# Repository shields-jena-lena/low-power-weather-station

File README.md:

# low-power-weather-station
Circuity and code for a low-power weather station design used for agricultural research

Build instructions will be available in Hardware X article once published

https://doi.org/10.5281/zenodo.22212162

# File summaries:

## 3.1	Arduino_code: different code versions to upload to weather station boards
  -	weatherstation_v2.ino
    - Arduino code to run the second version of the weather station build, this version allows for sleep.
  -	weatherstation_v2_constant.ino
    - Arduino code to run the second version of the weather station build, data is taken continuously.
  -	weatherstation_v5.ino
    -	Arduino code the run the 5th version of the weather station build, this version allows sleep and includes more code for low power optimization.
  -	Weatherstation_v5_constant.ino
    -	Arduino code to run the 5th version of the weather station build, data is taken continuously.

## 3.2	CAD_files: .stl files for 3D printed sensor box
  -	Humidity box bottom 1.stl
    -	STL file to print the bottom half of the box to hold the humidity and temperature sensor.
  -	Humidity box top 1.stl
    - STL file to print the top half of the box to hold the humidity and temperature sensor.

## 3.3	KiCAD_files: Circuit design and PCB design for custom circuity for weather stations
  -	Libraries
    -	Footprints and symbols for electronic components custom designed or downloaded from digikey.
  -	weather_station_v2
    -	Complete KiCAD project files for the design and PCB layout of the 2nd version of the weather station. Includes the schematic, project file, board design, bill of materials, backups, custom_footprints, and gerber files.
  -	weather_station_v5
    -	Complete KiCAD project files for the design and PCB layout of the 5th version of the weather station. Includes the schematic, project file, board design, bill of materials, backups, and gerber files.
      
## 3.4	Matlab_code – Matlab scripts to calibrate, process, and analyze weather station data, includes sample data
  -	txtfile_to_table.m
    -	MATLAB script to convert raw data from Arduino output to a .mat table.
  -	txtfile_to_table_parpool.m
    -	MATLAB script to convert raw data from Arduino output to a .mat table, using parpool to loop through all raw data in one script.
  -	std_omidNaN.m
    -	Custom function to support other MATLAB scripts that need the standard deviation while omitting NaN values.
  -	makebigarray.m
    -	MATLAB script to take the .mat tables of each weather station and combine into a large array with data from all the stations.
  -	field_analysis.m
    -	MATLAB script to do some basic analysis on the data in the large array created by makebigarray.m.
  -	calibrate_cupanemometer.m 
    - MATLAB script to calibrate cup anemometers if you have test chamber with known wind speed and raw cup count data from the weather stations. 
  -	sample_data (Both in Matlab_code/ and in Python_code/)
    - Raw text file data from weather stations. Each data file is labeled “weather_station_b#” where # is the number of the station. Data from stations 3 through 7 is included. The station_heights.csv file reports the height of the wind measurements and temperature/humidity measurements for each station. The image field28_layout_8-29-23 shows the relative location of each station to each other. The calibration_data folder includes raw data from each weather station in a testing chamber with known wind speed.
       
## 3.5	Python_code – Python scripts to calibrate, process, and analyze wather station data, includes sample data
  -	txtfile_to_table.py
    -	Python script to convert raw data from weather station to .csv file. 
  -	txtfile_to_table_forloop.py
    -	Python script to convert raw data from weather station to .csv file, a for loop is used to loop through all weather stations in one script.
  -	makebigarray.py
    -	Python script to take the .csv tables of each weather station and combine into a large array with data from all the stations.
  -	fieldanalysis.py
    -	Python script to take the output of makebigarray.py and do some basic analysis.
  -	calibrate_cupanemometer.py
    -	Python script to calibrate cup anemometer if you have test chamber with known wind speed and raw cup count data from the weather stations. 
  -	sample_data (Both in Matlab_code/ and in Python_code/)
    -	Raw text file data from weather stations. Each data file is labeled “weather_station_b#” where # is the number of the station. Data from stations 3 through 7 is included. The station_heights.csv file reports the height of the wind measurements and temperature/humidity measurements for each station. The image field28_layout_8-29-23 shows the relative location of each station to each other. The calibration_data folder includes raw data from each weather station in a testing chamber with known wind speed.

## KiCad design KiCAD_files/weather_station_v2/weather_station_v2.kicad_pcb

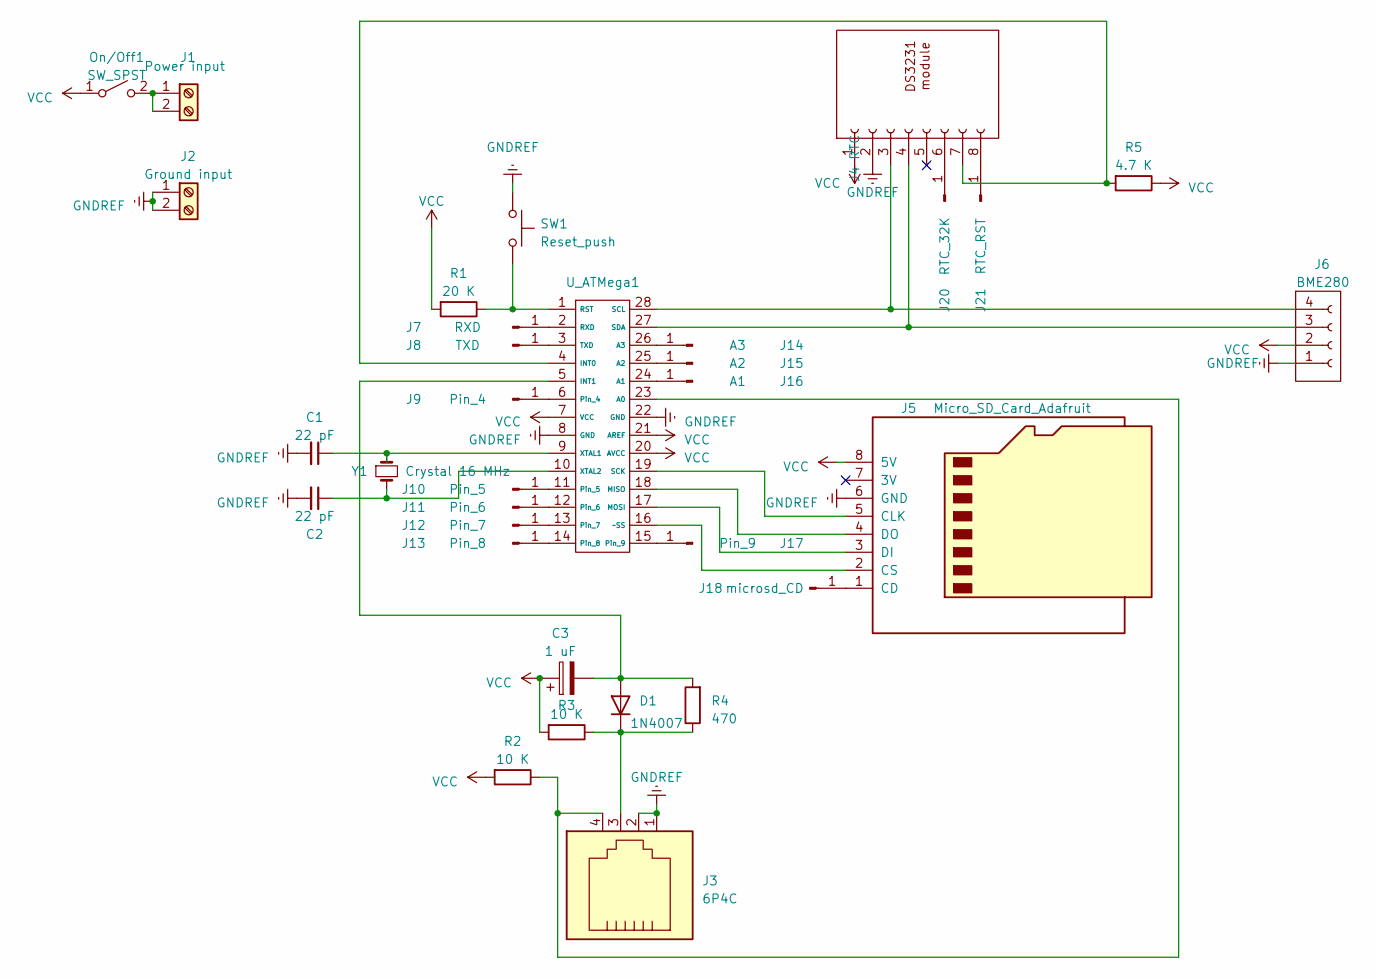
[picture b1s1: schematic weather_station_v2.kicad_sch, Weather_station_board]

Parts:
C1, C2: 22 pF; C_1206_3216Metric_Pad1.33x1.80mm_HandSolder
C3: 1 uF; C_Elec_4x5.4
D1: 1N4007; D_SOD-123F
J1: Power input; Term_Block_1x2_P5.08MM
J2: Ground input; Term_Block_1x2_P5.08MM
J3: 6P4C; RJ11_connector_jack
J4: RTC; PinSocket_1x08_P2.54mm_Vertical_RTC
J5: Micro_SD_Card_Adafruit; adafruit_microSD_breakout_board_8-pin
J6: BME280; JST-SH
J7: RXD; Pin_D1.0mm_L10.0mm
J8: TXD; Pin_D1.0mm_L10.0mm
J9: Pin_4; Pin_D1.0mm_L10.0mm
J10: Pin_5; Pin_D1.0mm_L10.0mm
J11: Pin_6; Pin_D1.0mm_L10.0mm
J12: Pin_7; Pin_D1.0mm_L10.0mm
J13: Pin_8; Pin_D1.0mm_L10.0mm
J14: A3; Pin_D1.0mm_L10.0mm
J15: A2; Pin_D1.0mm_L10.0mm
J16: A1; Pin_D1.0mm_L10.0mm
J17: Pin_9; Pin_D1.0mm_L10.0mm
J18: microsd_CD; Pin_D1.0mm_L10.0mm
J20: RTC_32K; Pin_D1.0mm_L10.0mm
J21: RTC_RST; Pin_D1.0mm_L10.0mm
On/Off1: SW_SPST; Switch_Slide_SPST_DS04-254-2-01BK-SMT
R1: 20 K; R_1206_3216Metric_Pad1.30x1.75mm_HandSolder
R2, R3: 10 K; R_1206_3216Metric_Pad1.30x1.75mm_HandSolder
R4: 470; R_1206_3216Metric_Pad1.30x1.75mm_HandSolder
R5: 4.7 K; R_1206_3216Metric_Pad1.30x1.75mm_HandSolder
SW1: Reset_push; SW_Tactile_SPST_NO_Straight_CK_PTS636Sx25SMTRLFS
U_ATMega1: Socket_DIP-28_7.62mm_Conn
Y1: Crystal 16 MHz; Crystal_HC18-U_Vertical

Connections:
GNDREF: C1.2, C2.2, J2.1, J2.2, J3.1, J3.2, J4.2 (GND), J5.6 (GND), J6.1, SW1.1, U_ATMega1.8 (GND), U_ATMega1.22 (GND)
unnamed: C3.2, D1.2 (A), R4.2, U_ATMega1.5 (INT1)
unnamed: D1.1 (K), J3.3, R3.1, R4.1
unnamed: J1.1, J1.2, On/Off1.2 (B)
unnamed: J4.3 (SCL), J6.4, U_ATMega1.28 (SCL)
unnamed: J4.4 (SDA), J6.3, U_ATMega1.27 (SDA)
unnamed: J4.7 (SQW), R5.2, U_ATMega1.4 (INT0)
unnamed: J5.5 (CLK), U_ATMega1.19 (SCK)
unnamed: J5.2 (CS), U_ATMega1.16 (~SS)
unnamed: J5.3 (DI), U_ATMega1.17 (MOSI)
unnamed: J5.4 (DO), U_ATMega1.18 (MISO)
unnamed: J7.1, U_ATMega1.2 (RXD)
unnamed: J8.1, U_ATMega1.3 (TXD)
unnamed: J9.1, U_ATMega1.6 (Pin_4)
unnamed: J10.1, U_ATMega1.11 (Pin_5)
unnamed: J11.1, U_ATMega1.12 (Pin_6)
unnamed: J12.1, U_ATMega1.13 (Pin_7)
unnamed: J13.1, U_ATMega1.14 (Pin_8)
unnamed: J14.1, U_ATMega1.26 (A3)
unnamed: J15.1, U_ATMega1.25 (A2)
unnamed: J16.1, U_ATMega1.24 (A1)
unnamed: J17.1, U_ATMega1.15 (Pin_9)
unnamed: J5.1 (CD), J18.1
unnamed: J4.6 (32K), J20.1
unnamed: J4.8 (RST), J21.1
unnamed: J3.4, R2.1, U_ATMega1.23 (A0)
unnamed: R1.1, SW1.2, U_ATMega1.1 (RST)
unnamed: C1.1, U_ATMega1.9 (XTAL1), Y1.1
unnamed: C2.1, U_ATMega1.10 (XTAL2), Y1.2
VCC: C3.1, J4.1 (Vin), J5.8 (5V), J6.2, On/Off1.1 (A), R1.2, R2.2, R3.2, R5.1, U_ATMega1.7 (VCC), U_ATMega1.20 (AVCC), U_ATMega1.21 (AREF)

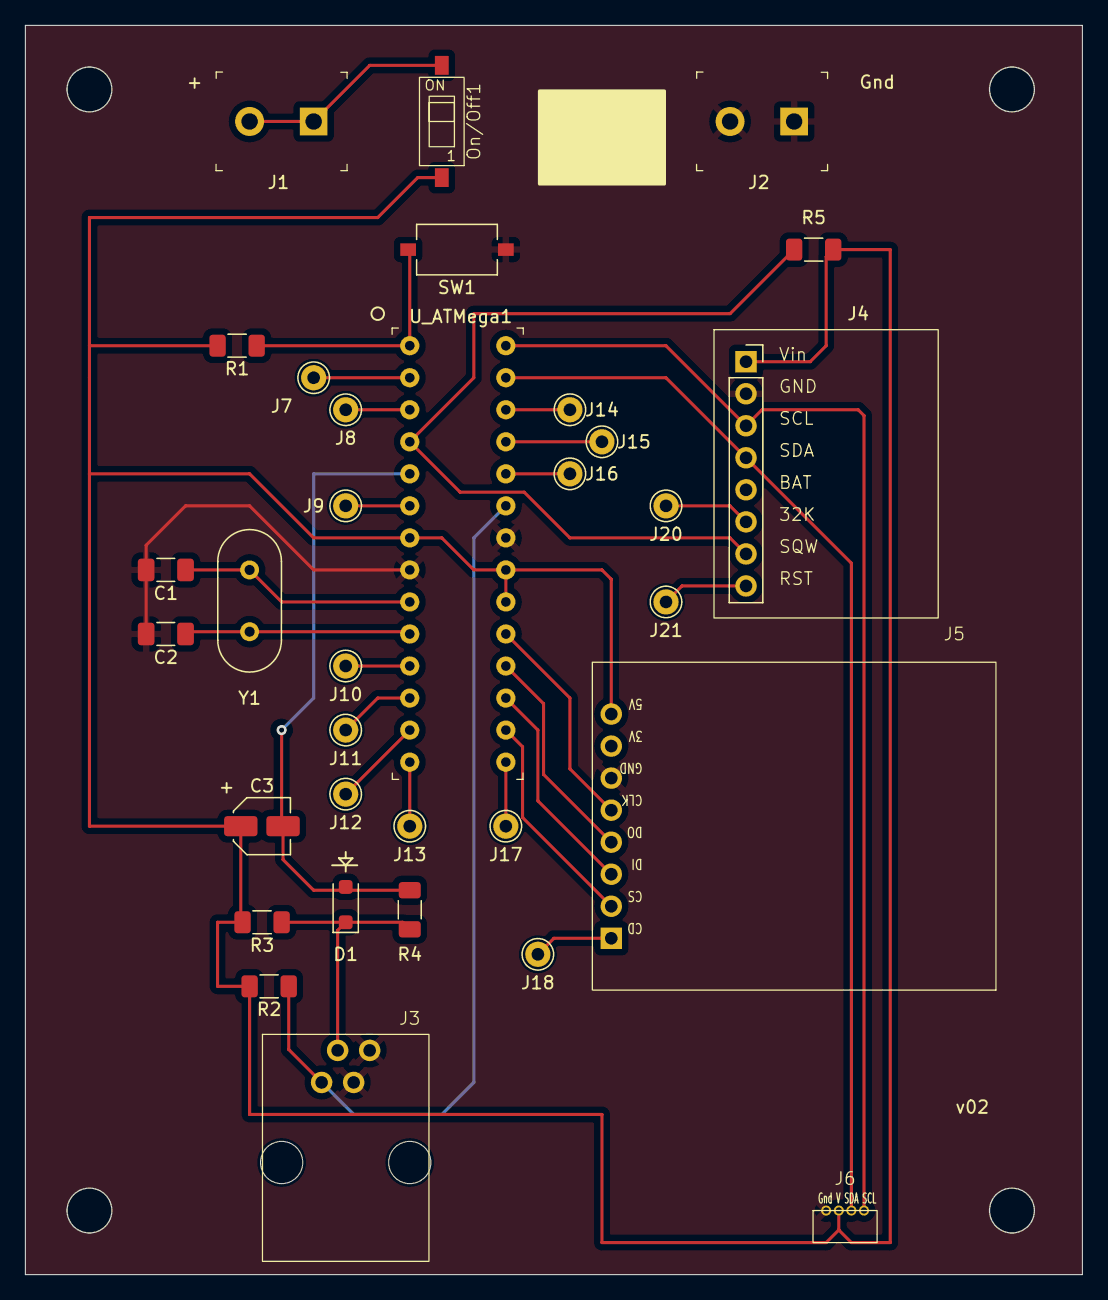
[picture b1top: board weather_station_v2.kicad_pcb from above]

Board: 2 copper layers, 83.7 x 99.0 mm, 33 parts (0 on the bottom side), 30 nets.

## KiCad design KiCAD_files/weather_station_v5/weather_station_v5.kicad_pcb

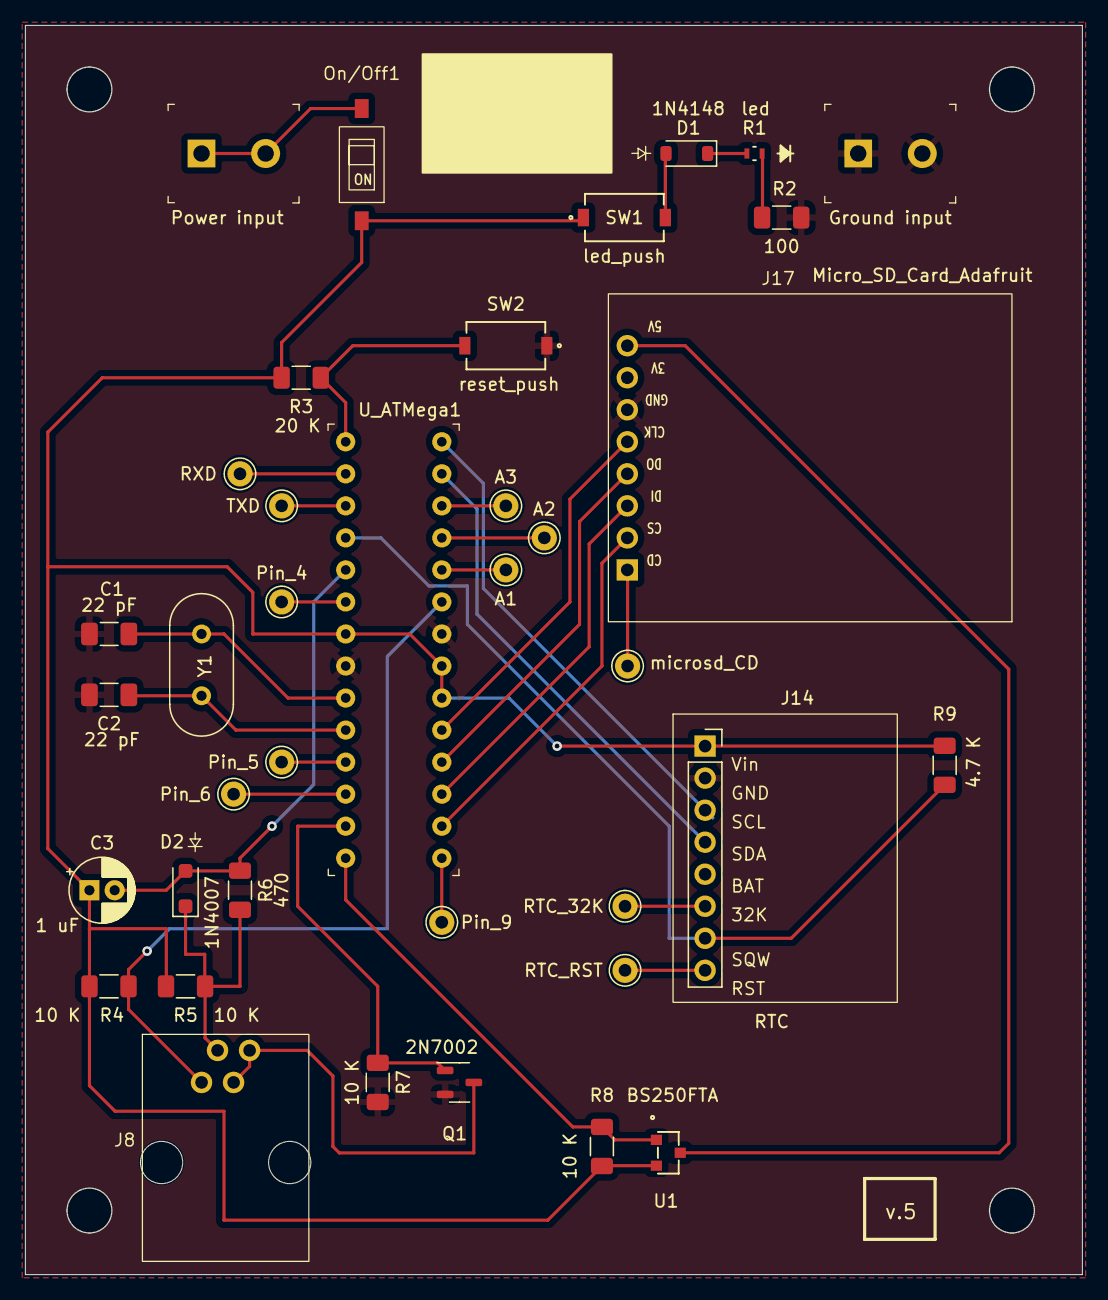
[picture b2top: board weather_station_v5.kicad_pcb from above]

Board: 2 copper layers, 83.7 x 99.0 mm, 38 parts (0 on the bottom side), 35 nets.

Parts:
C1, C2: 22 pF; C_1206_3216Metric_Pad1.33x1.80mm_HandSolder
C3: 1 uF; CP_Radial_D5.0mm_P2.00mm
D1: 1N4148; D_SOD-123
D2: 1N4007; D_SOD-123F
J1: Power input; Term_Block_1x2_P5.08MM
J2: Ground input; Term_Block_1x2_P5.08MM
J3: RXD; Pin_D1.0mm_L10.0mm
J4: TXD; Pin_D1.0mm_L10.0mm
J5: Pin_4; Pin_D1.0mm_L10.0mm
J6: Pin_5; Pin_D1.0mm_L10.0mm
J7: Pin_6; Pin_D1.0mm_L10.0mm
J8: 6P4C; RJ11_connector_jack
J9: A3; Pin_D1.0mm_L10.0mm
J10: A2; Pin_D1.0mm_L10.0mm
J11: A1; Pin_D1.0mm_L10.0mm
J12: Pin_9; Pin_D1.0mm_L10.0mm
J13: microsd_CD; Pin_D1.0mm_L10.0mm
J14: RTC; PinSocket_1x08_P2.54mm_Vertical_RTC
J15: RTC_32K; Pin_D1.0mm_L10.0mm
J16: RTC_RST; Pin_D1.0mm_L10.0mm
J17: Micro_SD_Card_Adafruit; adafruit_microSD_breakout_board_8-pin
On/Off1: SW_SPST; Switch_Slide_SPST_DS04-254-2-01BK-SMT
Q1: 2N7002; SOT-23-3
R1: led; LED_SMLD12_ROM
R2: 100; R_1206_3216Metric_Pad1.30x1.75mm_HandSolder
R3: 20 K; R_1206_3216Metric_Pad1.30x1.75mm_HandSolder
R4, R5, R7, R8: 10 K; R_1206_3216Metric_Pad1.30x1.75mm_HandSolder
R6: 470; R_1206_3216Metric_Pad1.30x1.75mm_HandSolder
R9: 4.7 K; R_1206_3216Metric_Pad1.30x1.75mm_HandSolder
SW1: led_push; SW_PTS636_CNK
SW2: reset_push; SW_PTS636_CNK
U1: BS250FTA; SOT-23_DIO
U_ATMega1: Socket_DIP-28_7.62mm_Conn
Y1: Crystal 16 MHz; Crystal_HC18-U_Vertical

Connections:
GNDREF: C1.2, C2.2, J2.1, J2.2, J14.2 (GND), J17.6 (GND), Q1.2 (S), R2.2, R7.2, SW2.1, U_ATMega1.8 (GND), U_ATMega1.22 (GND)
unnamed: D1.2 (A), SW1.2
unnamed: D1.1 (K), R1.2
unnamed: C3.2, D2.2 (A), R6.2, U_ATMega1.5 (INT1)
unnamed: D2.1 (K), J8.3, R5.1, R6.1
unnamed: J1.1, J1.2, On/Off1.2 (B)
unnamed: J3.1, U_ATMega1.2 (RXD)
unnamed: J4.1, U_ATMega1.3 (TXD)
unnamed: J5.1, U_ATMega1.6 (Pin_4)
unnamed: J6.1, U_ATMega1.11 (Pin_5)
unnamed: J7.1, U_ATMega1.12 (Pin_6)
unnamed: J9.1, U_ATMega1.26 (A3)
unnamed: J10.1, U_ATMega1.25 (A2)
unnamed: J11.1, U_ATMega1.24 (A1)
unnamed: J12.1, U_ATMega1.15 (Pin_9)
unnamed: J13.1, J17.1 (CD)
unnamed: J14.6 (32K), J15.1
unnamed: J14.8 (RST), J16.1
unnamed: J14.3 (SCL), U_ATMega1.28 (SCL)
unnamed: J14.4 (SDA), U_ATMega1.27 (SDA)
unnamed: J14.7 (SQW), R9.2, U_ATMega1.4 (INT0)
unnamed: J17.8 (5V), U1.1 (D)
unnamed: J17.5 (CLK), U_ATMega1.19 (SCK)
unnamed: J17.2 (CS), U_ATMega1.16 (~SS)
unnamed: J17.3 (DI), U_ATMega1.17 (MOSI)
unnamed: J17.4 (DO), U_ATMega1.18 (MISO)
unnamed: J8.1, J8.2, Q1.3 (D)
unnamed: Q1.1 (G), R7.1, U_ATMega1.13 (Pin_7)
unnamed: R1.1, R2.1
unnamed: R8.1, U1.2 (G), U_ATMega1.14 (Pin_8)
unnamed: J8.4, R4.1, U_ATMega1.23 (A0)
unnamed: R3.1, SW2.2, U_ATMega1.1 (RST)
unnamed: C1.1, U_ATMega1.9 (XTAL1), Y1.1
unnamed: C2.1, U_ATMega1.10 (XTAL2), Y1.2
VCC: C3.1, J14.1 (Vin), On/Off1.1 (A), R3.2, R4.2, R5.2, R8.2, R9.1, SW1.1, U1.3 (S), U_ATMega1.7 (VCC), U_ATMega1.20 (AVCC), U_ATMega1.21 (AREF)

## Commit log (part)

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2025-05-27 Upload and comment weatherstation_field_lowpower.ino
    Uploaded the current version of the low power weather station code. Commented out the code for readability.
2025-05-27 Update weatherstation_field_lowpower.ino
    Removed excess spaces
2025-05-27 Update alarm in weatherstation_field_lowpower.ino
    Make it more user friendly to change the alarm type.
2025-06-15 KiCad and arduino files added, matlab edited
    Added kicad files of schematic and PCB board design to folder. Edited matlab scripts, added arduino scripts. Need to keep working on all.
2025-06-16 Upload old materials, comment codes
    Add kicad files for v2 build, add/comment on arduino codes for both versions, add a continuous version for v5. Finish commenting matlab codes and add calibration data for the 5 stations.
